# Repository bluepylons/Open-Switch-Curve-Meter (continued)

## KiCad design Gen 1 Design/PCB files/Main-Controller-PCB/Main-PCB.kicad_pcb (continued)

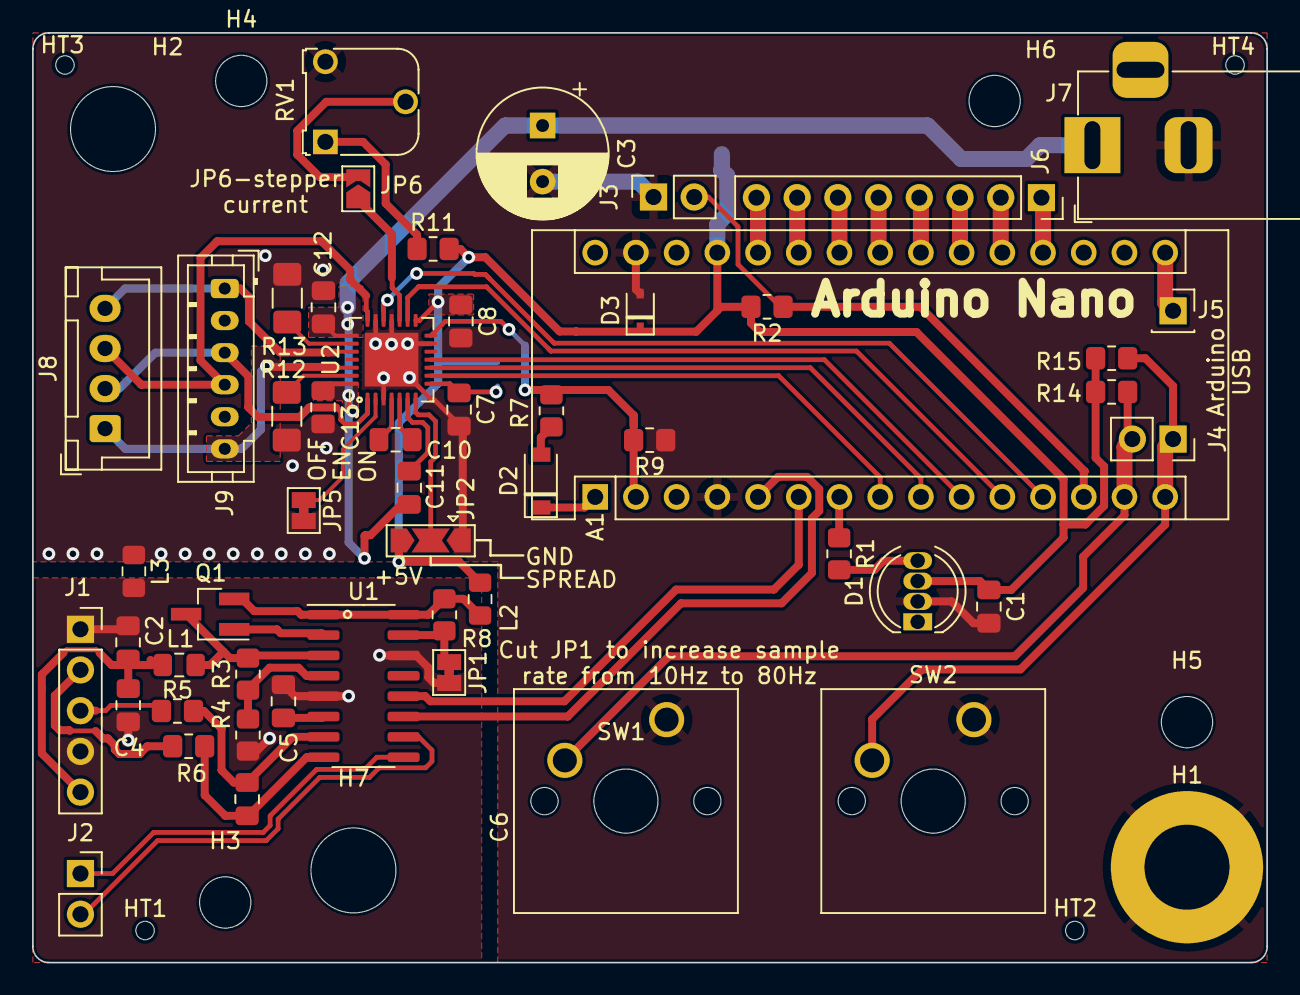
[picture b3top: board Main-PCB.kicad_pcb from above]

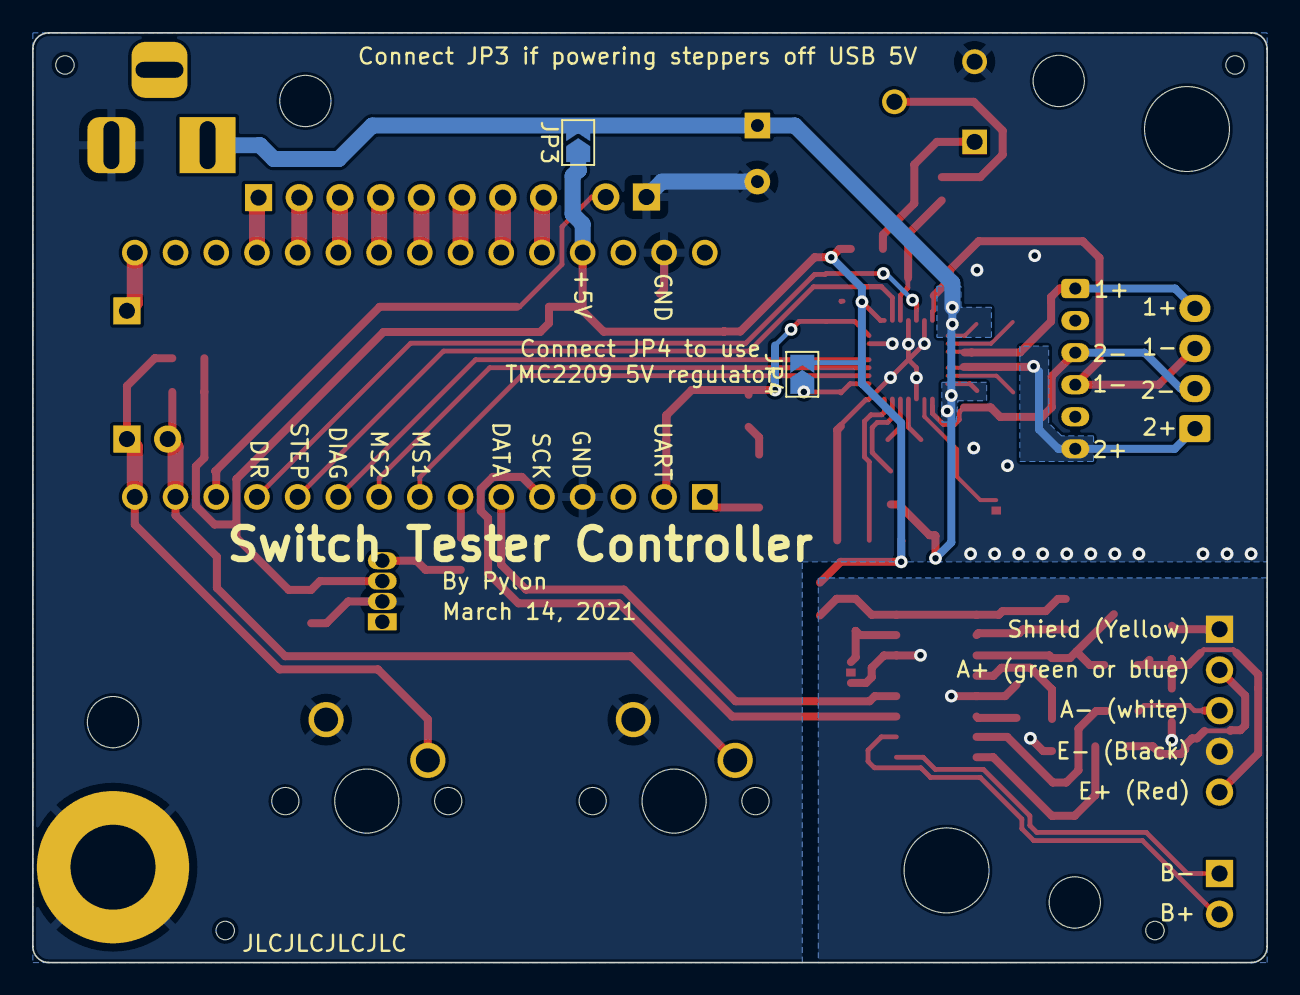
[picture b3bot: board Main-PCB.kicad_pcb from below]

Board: 2 copper layers, 77.0 x 58.0 mm, 65 parts (2 on the bottom side), 56 nets.

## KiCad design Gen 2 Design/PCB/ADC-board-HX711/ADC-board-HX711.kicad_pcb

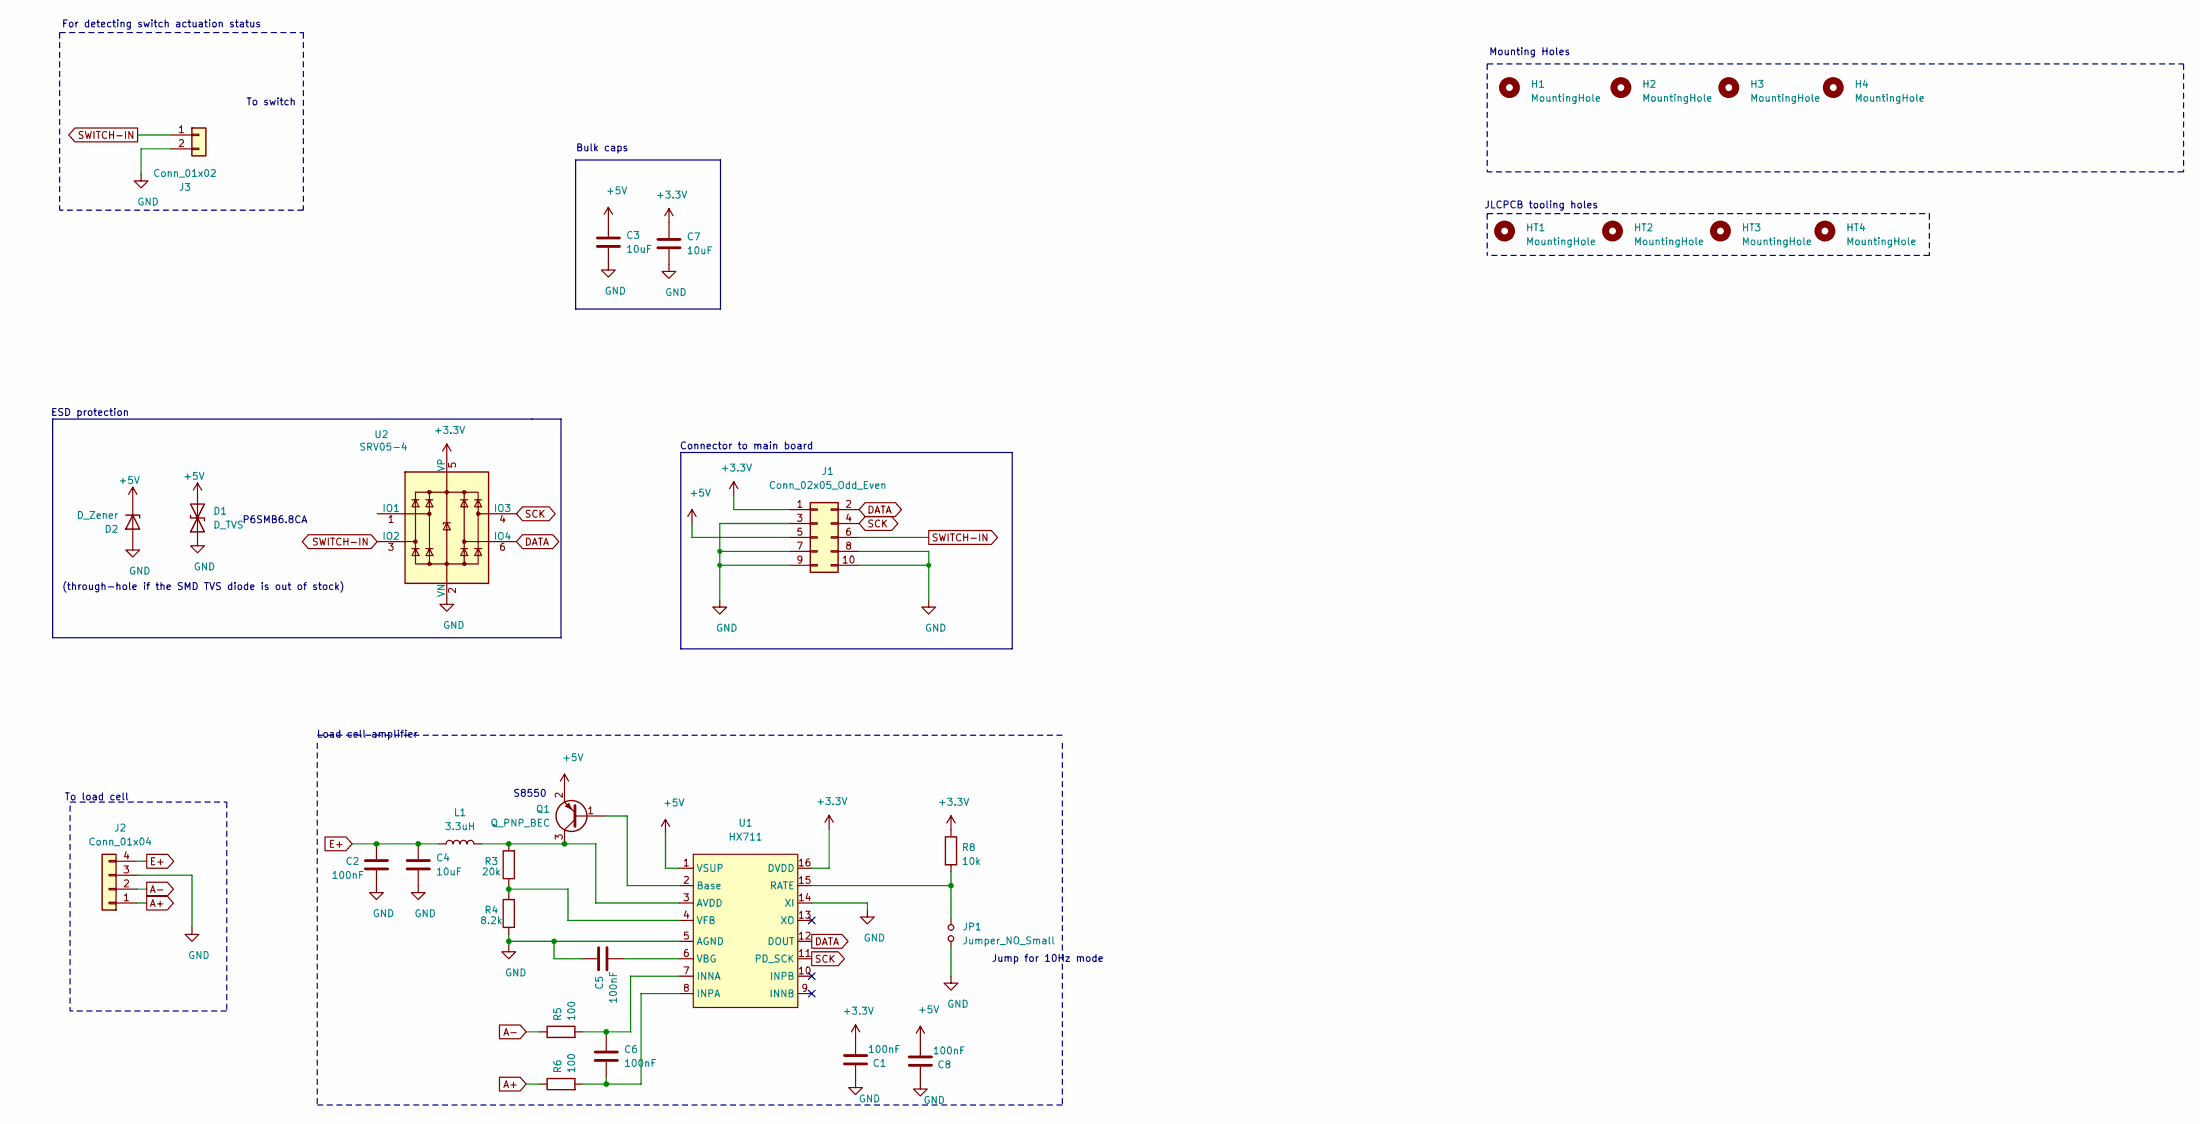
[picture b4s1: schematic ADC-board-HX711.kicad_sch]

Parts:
C1, C2, C5, C6, C8: 100nF; C_0805_2012Metric_Pad1.18x1.45mm_HandSolder
C3, C4, C7: 10uF; C_1206_3216Metric_Pad1.33x1.80mm_HandSolder
D1: D_TVS; D_SMB_Handsoldering
D2: D_Zener; D_DO-41_SOD81_P7.62mm_Horizontal
H1, H2, H3, H4: MountingHole; MountingHole_3.2mm_M3_ISO7380
HT1, HT2, HT3, HT4: MountingHole; ToolingHole_1.152mm_(for_JLCPCB_SMT)
J1: Conn_02x05_Odd_Even; 2x05-P2.54mm-Shrouded-Keyed-Header
J2: Conn_01x04; TerminalBlock_Phoenix_MKDS-1,5-4_1x04_P5.00mm_Horizontal
J3: Conn_01x02; TerminalBlock_Phoenix_MKDS-1,5-2_1x02_P5.00mm_Horizontal
JP1: Jumper_NO_Small; SolderJumper-2_P1.3mm_Open_RoundedPad1.0x1.5mm
L1: 3.3uH; L_0805_2012Metric_Pad1.15x1.40mm_HandSolder
Q1: Q_PNP_BEC; SOT-23_Handsoldering
R3: 20k; R_0805_2012Metric_Pad1.20x1.40mm_HandSolder
R4: 8.2k; R_0805_2012Metric_Pad1.20x1.40mm_HandSolder
R5, R6: 100; R_0805_2012Metric_Pad1.20x1.40mm_HandSolder
R8: 10k; R_0805_2012Metric_Pad1.20x1.40mm_HandSolder
U1: HX711; SOP-16_3.9x9.9mm_P1.27mm
U2: SRV05-4; SOT-23-6

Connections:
+3V3: C1.2, C7.1, J1.1, R8.1, U1.16 (DVDD), U2.5 (VP)
+5V: C3.1, C8.2, D1.2 (A2), D2.1 (K), J1.5, Q1.2 (E), U1.1 (VSUP)
A+: J2.1, R6.1
A-: J2.2, R5.1
DATA: J1.2, U1.12 (DOUT), U2.6 (IO4)
E+: C2.1, C4.1, J2.4, L1.1
GND: C1.1, C2.2, C3.2, C4.2, C5.1, C7.2, C8.1, D1.1 (A1), D2.2 (A), J1.3, J1.7, J1.8, J1.9, J1.10, J2.3, J3.2, JP1.1, R4.1, U1.5 (AGND), U1.14 (XI), U2.2 (VN)
unnamed: C5.2, U1.6 (VBG)
unnamed: C6.1, R5.2, U1.7 (INNA)
unnamed: C6.2, R6.2, U1.8 (INPA)
unnamed: JP1.2, R8.2, U1.15 (RATE)
unnamed: L1.2, Q1.3 (C), R3.2, U1.3 (AVDD)
unnamed: Q1.1 (B), U1.2 (Base)
unnamed: R3.1, R4.2, U1.4 (VFB)
SCK: J1.4, U1.11 (PD_SCK), U2.4 (IO3)
SWITCH-IN: J1.6, J3.1, U2.3 (IO2)

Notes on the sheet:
To switch
JLCPCB tooling holes
P6SMB6.8CA
(through-hole if the SMD TVS diode is out of stock)
To load cell
Mounting Holes
Connector to main board
Jump for 10Hz mode
Bulk caps
ESD protection
Load cell amplifier
For detecting switch actuation status
S8550

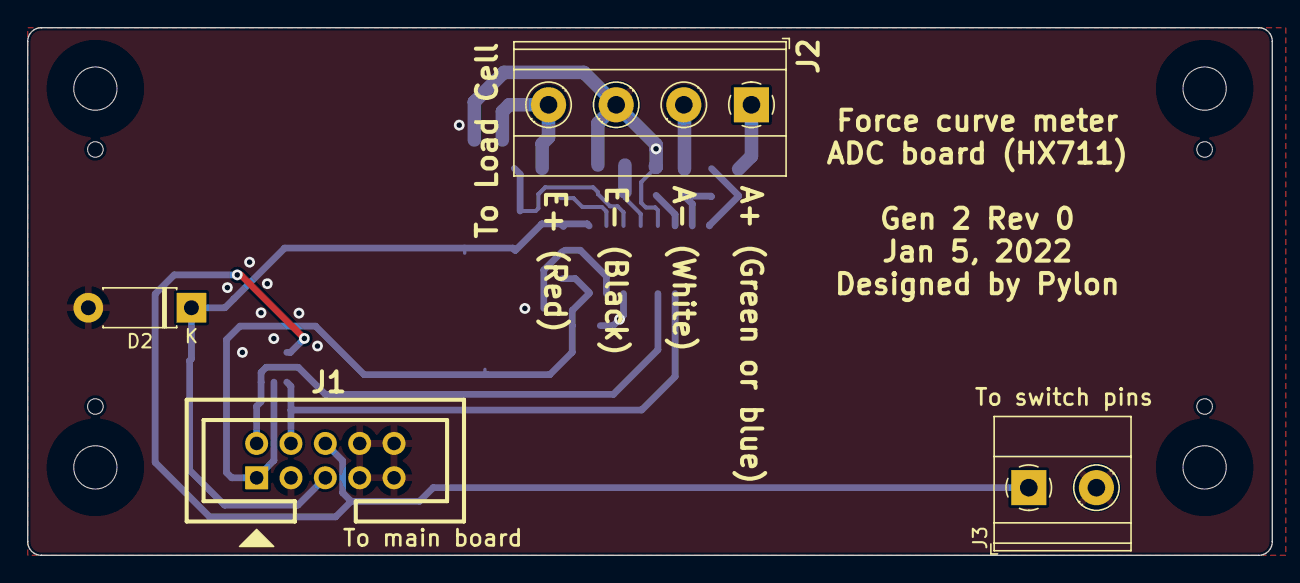
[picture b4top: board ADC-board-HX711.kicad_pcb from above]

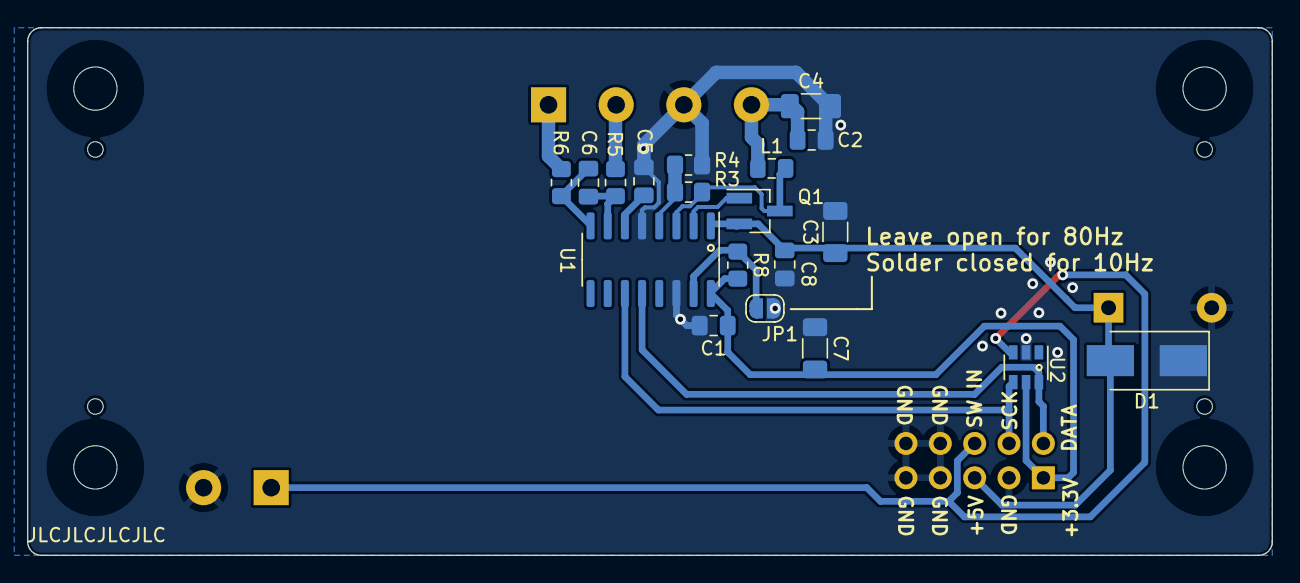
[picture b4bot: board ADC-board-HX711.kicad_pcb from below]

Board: 2 copper layers, 92.0 x 39.0 mm, 31 parts (23 on the bottom side), 16 nets.

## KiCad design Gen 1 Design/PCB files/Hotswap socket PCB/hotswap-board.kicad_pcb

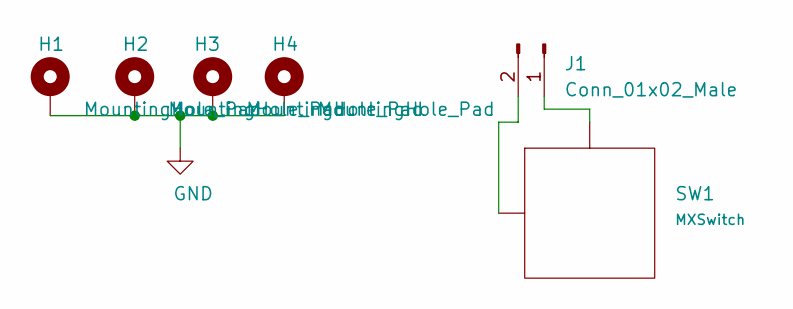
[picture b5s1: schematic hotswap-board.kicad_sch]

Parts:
H1, H2, H3, H4: MountingHole_Pad; MountingHole_3.2mm_M3_ISO7380_Pad
J1: Conn_01x02_Male; PinHeader_2x01_P2.54mm_Vertical
SW1: MXSwitch; MX100H

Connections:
GND: H1.1, H2.1, H3.1, H4.1
unnamed: J1.1, SW1.2 (Row)
unnamed: J1.2, SW1.1 (Col)

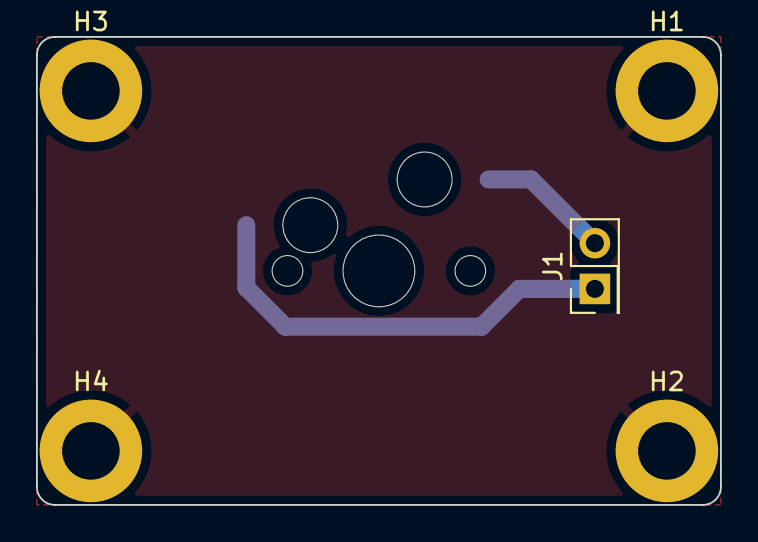
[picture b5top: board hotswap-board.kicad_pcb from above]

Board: 2 copper layers, 38.0 x 26.0 mm, 6 parts (1 on the bottom side), 3 nets.

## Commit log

2021-06-18 Wiping commit history
2021-06-20 Added Polia stem in Zealio housing with Cherry top
2021-06-20 Added Polia stem in Zealio V2 bottom, Cherry top
2021-06-25 Added U4T vs Polia vs Halo stem
2021-06-25 Added Tecsee Blue Velvet linear stem in JWK Lavender housing
2021-06-27 Clarified that the Gateron Kangaroo is the Novelkeys version
2021-07-03 Added several switches
2021-08-04 Added Rebult switches
2021-08-04 Fixed formatting issue around Moyu Black
2021-08-04 Added Moyu Studio x JWK Queen
2021-08-04 Added T1 Dark Amber (forgot to include on README)
2021-08-05 Added regular Durock T1 and T1 stem in Harimau
2021-08-05 Added some force curves I forgot to add
2021-08-05 Added note on Dark Amber T1 that it has the "V1" housing
2021-08-05 Fixed legend in Boba U4 68G
2021-08-05 Fixed some typos, added Rebult Keyboards to donors of switches
2021-08-08 Fixed minor formatting issue for KK LIghtwave V2
2021-08-18 Fixed mistake where graph for Polia stem in Zealio V2 bottom wasn't showing
2021-08-18 Added various raw graphs
2021-08-22 Added feature to re-measure in case of HX711 error
2021-08-22 Added large number of switches Dangkeebs sent me
2021-08-22 Forgot to note these were measured with the leaf removed
2021-08-22 Added various frankenswitches
2021-08-22 Added a bunch of frankenswitches
2021-08-22 Updated README with new switch measurements
2021-08-22 Fixed some typos
2021-08-24 Changed Moyu Studio to Moyu.studio
2021-08-24 Added 2 switches
2021-08-24 Forgot to post updated ODS
2021-08-24 Renamed file names to Moyu-JWK-Poseidon
2023-04-24 Reinitializing
2024-01-19 Clarified WIP
2024-04-18 Updated some comments
2024-04-18 Updated to KiCAD 8
2024-04-18 Made Arduino Nano variant of the main board
2024-04-18 Forgot to plot reference designators
2024-04-20 More work; organization
2025-10-15 Some reorganization
2025-10-15 Measured Cherry MX Purple
2025-10-15 Rename
2025-10-15 Add Cherry MX Purple RGB
2025-10-15 Clarified Cherry MX Purple is MX2A
2025-10-15 Add Futaba MA-41
2025-10-16 Made new graphs the same size as the old graphs
2025-10-18 Added a protection bracket for the load cell
2025-10-29 Added Gateron Melodic
2025-11-27 Add images
2025-11-27 Minor PCB fixes
    Changed Start_switch pin to A0, as D13 (original assignment) cannot be set to INPUT_PULLUP
2025-11-28 General update
2025-11-28 Missing )
2025-12-06 Fixed silkscreen, connected J5 on PCB
2025-12-06 Replaced Misumi HFS5 CAD models with ones done from scratch
2025-12-15 Some work on the CAD file
2026-01-05 Generally update CAD model
2026-01-06 Partial update
2026-01-06 Rename folder
2026-01-06 Move folder
2026-01-06 Move file
2026-01-06 Updated STLs
2026-01-06 Slotted linear stage mounting holes on Vertical-plate to allow compatibility for other linear stages
2026-01-06 More work
2026-01-06 Added STEP files
2026-01-08 Fixed some typos/errors
2026-01-17 New pics
2026-01-17 Added pic without keycap
2026-01-18 Removed outdated
2026-04-12 Clarify comments
